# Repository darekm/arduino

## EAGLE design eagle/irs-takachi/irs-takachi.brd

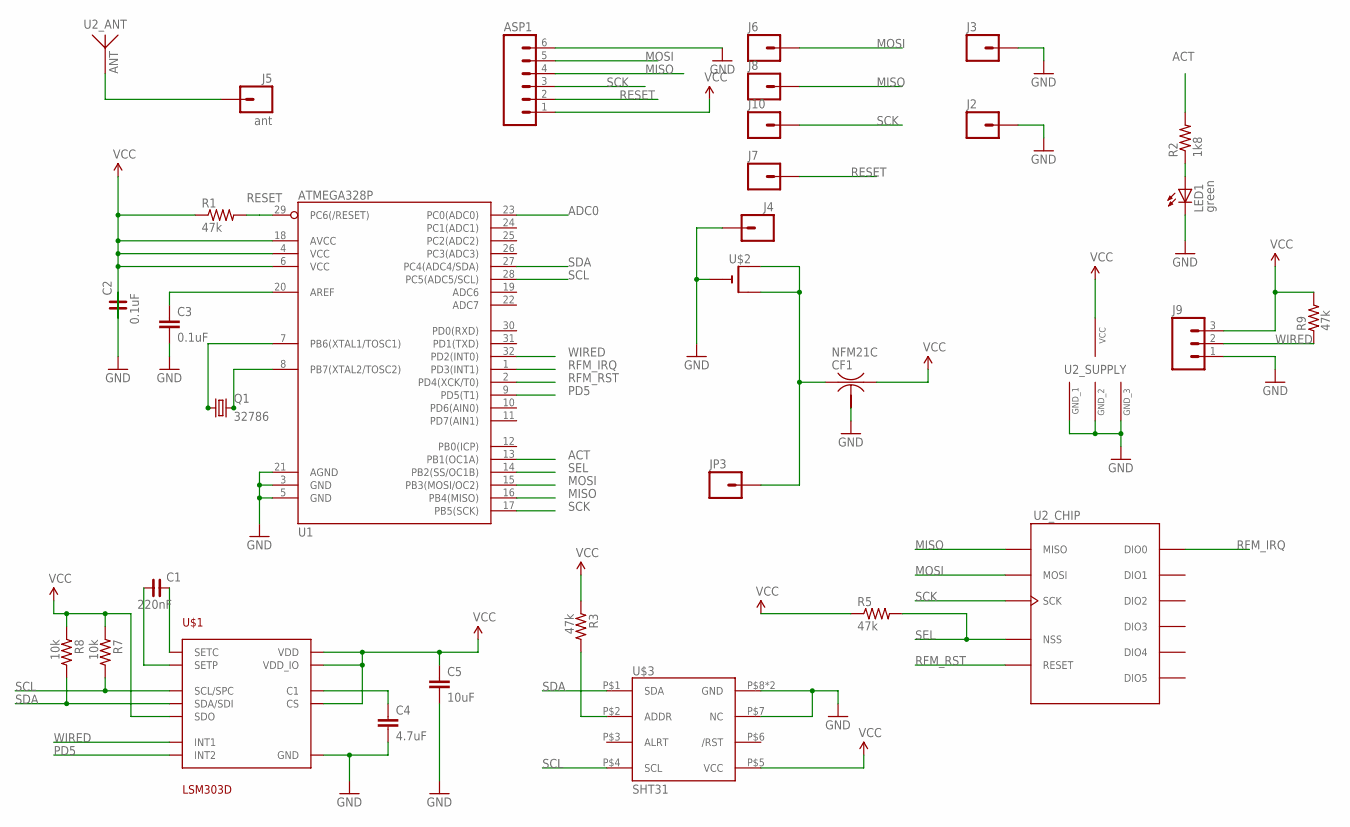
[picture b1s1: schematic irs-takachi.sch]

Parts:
ASP1: M06NO_SILK_YES_STOP; 1X06_NO_SILK_YES_STOP
C1: 220nF; C0603
C2: 0.1uF; C0603
C3: 0.1uF; 0603-CAP
C4: 4.7uF; C0603K
C5: 10uF; 0805-CAP
CF1: NFM21C
J2, J3: M01PTH_NO_SILK_YES_STOP; 1X01_NO_SILK
J4: M01SNAP-FEMALE; SNAP-FEMALE
J5: ant; 1X01_NO_SILK
J6, J7, J8, J10: M01SMD-4.5X1.5; PAD-1.5X4.5
J9: M031X03_NO_SILK; 1X03_NO_SILK
JP3: M01SMDNS; 1X01NS
LED1: green; LED-0603
Q1: 32786; MC-306
R1, R5: 47k; 0603-RES
R2: 1k8; 0603-RES
R3, R9: 47k; R0603
R7, R8: 10k; R0603
U1: ATMEGA328P; TQFP32-08
U2: RFM69HCW-S2; HOPE-RF-16
U$1: LSM303D; LGA16-3MM
U$2: CR2032THM; CR2032-THRU
U$3: SHT31; SHT3X

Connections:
ACT: R2.2, U1.13 (PB1(OC1A))
ADC0: U1.23 (PC0(ADC0))
GND: ASP1.6, C2.2, C3.2, C4.2, C5.2, CF1.2@1 (2), J2.1, J3.1, J4.1, J9.1, LED1.C, U1.3 (GND), U1.5 (GND), U1.21 (AGND), U2.GND1 (GND_1), U2.GND2 (GND_2), U2.GND3 (GND_3), U$1.5 (GND), U$1.10 (GND), U$1.12 (GND), U$1.13 (GND), U$1.16 (GND), U$2.-, U$3.P$7 (NC), U$3.P$8 (GND), U$3.PAD (GND)
MISO: ASP1.4, J8.P$1, U1.16 (PB4(MISO)), U2.MISO
MOSI: ASP1.5, J6.P$1, U1.15 (PB3(MOSI/OC2)), U2.MOSI
unnamed: LED1.A, R2.1
unnamed: CF1.1, JP3.1, U$2.+1 (+), U$2.+2 (+1)
unnamed: J5.1, U2.ANT
unnamed: C3.1, U1.20 (AREF)
unnamed: Q1.1, U1.7 (PB6(XTAL1/TOSC1))
unnamed: Q1.4 (2), U1.8 (PB7(XTAL2/TOSC2))
unnamed: C1.1, U$1.3 (SETP)
unnamed: C1.2, U$1.2 (SETC)
unnamed: C4.1, U$1.15 (C1)
unnamed: R3.2, U$3.P$2 (ADDR)
PD5: U1.9 (PD5(T1)), U$1.9 (INT2)
RESET: ASP1.2, J7.P$1, R1.2, U1.29 (PC6(/RESET))
RFM_IRQ: U1.1 (PD3(INT1)), U2.DIO0
RFM_RST: U1.2 (PD4(XCK/T0)), U2.RESET
SCK: ASP1.3, J10.P$1, U1.17 (PB5(SCK)), U2.SCK
SCL: R7.2, U1.28 (PC5(ADC5/SCL)), U$1.4 (SCL/SPC), U$3.P$4 (SCL)
SDA: R8.2, U1.27 (PC4(ADC4/SDA)), U$1.6 (SDA/SDI), U$3.P$1 (SDA)
SEL: R5.2, U1.14 (PB2(SS/OC1B)), U2.NSS
VCC: ASP1.1, C2.1, C5.1, CF1.3, J9.3, R1.1, R3.1, R5.1, R7.1, R8.1, R9.2, U1.4 (VCC), U1.6 (VCC), U1.18 (AVCC), U2.3.3V (VCC), U$1.1 (VDD_IO), U$1.7 (SDO), U$1.8 (CS), U$1.14 (VDD), U$3.P$5 (VCC)
WIRED: J9.2, R9.1, U1.32 (PD2(INT0)), U$1.11 (INT1)

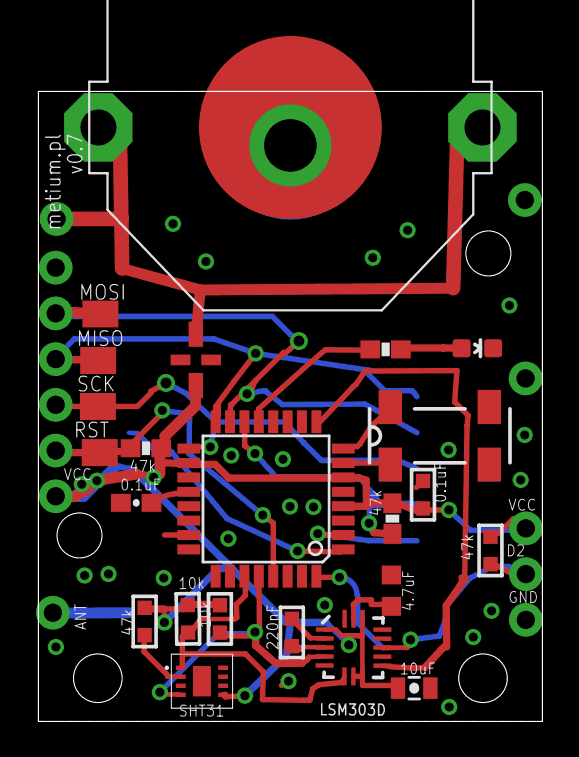
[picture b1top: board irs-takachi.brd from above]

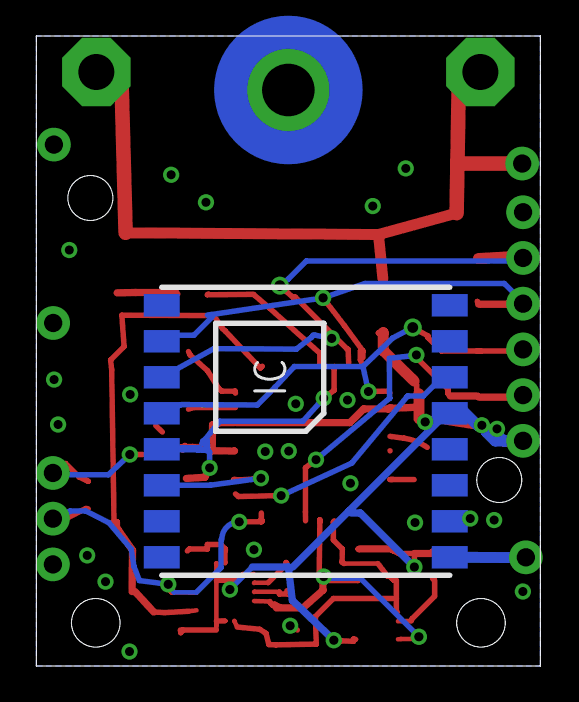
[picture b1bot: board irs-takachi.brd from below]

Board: 2 copper layers, 28.0 x 35.0 mm, 31 parts (3 on the bottom side), 24 nets.

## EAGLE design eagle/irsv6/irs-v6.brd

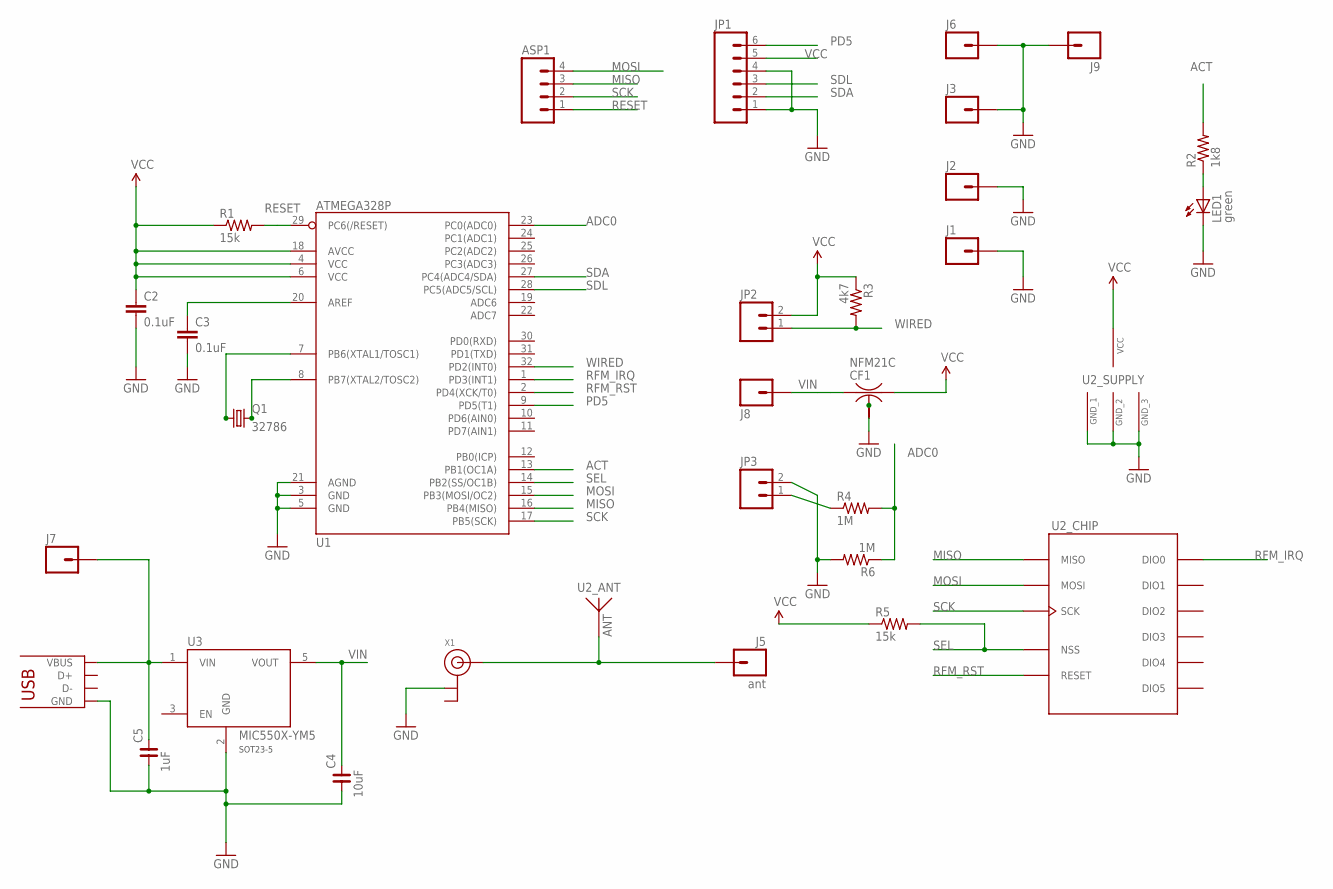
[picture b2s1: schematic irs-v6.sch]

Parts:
ASP1: M04NO_SILK_ALL_ROUND; 1X04_NO_SILK_ALL_ROUND
C2, C3: 0.1uF; 0603-CAP
C4: 10uF; C0805
C5: 1uF; C0805
CF1: NFM21C
J1, J2, J3, J6, J7, J8, J9: M01PTH_NO_SILK_YES_STOP; 1X01_NO_SILK
J4: USB-REVERSE-MICROB; USB-MICROB
J5: ant; 1X01_NO_SILK
JP1: M06NO_SILK_FEMALE_PTH; 1X06_NO_SILK
JP2, JP3: M021X02_NO_SILK; 1X02_NO_SILK
LED1: green; LED-0603
Q1: 32786; MC-306
R1, R5: 15k; 0603-RES
R2: 1k8; 0603-RES
R3: 4k7; 0603-RES
R4, R6: 1M; 0603-RES
U1: ATMEGA328P; TQFP32-08
U2: RFM69HCW-S2; HOPE-RF-16
U3: MIC550X-YM5; SOT23-5-DBV
X1: ANTENNA_U.FL; U.FL

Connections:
ACT: R2.2, U1.13 (PB1(OC1A))
ADC0: R4.2, R6.1, U1.23 (PC0(ADC0))
GND: C2.2, C3.2, C4.1, C5.1, CF1.2@1 (2), J1.1, J2.1, J3.1, J4.MT1 (GND), J4.MT2 (GND), J4.VBUS (GND), J6.1, J9.1, JP1.1, JP1.4, JP3.2, LED1.C, R6.2, U1.3 (GND), U1.5 (GND), U1.21 (AGND), U2.GND1 (GND_1), U2.GND2 (GND_2), U2.GND3 (GND_3), U3.2 (GND), X1.1 (GND)
MISO: ASP1.3, U1.16 (PB4(MISO)), U2.MISO
MOSI: ASP1.4, U1.15 (PB3(MOSI/OC2)), U2.MOSI
unnamed: LED1.A, R2.1
unnamed: JP3.1, R4.1
unnamed: J5.1, U2.ANT, X1.3 (SIGNAL)
unnamed: C3.1, U1.20 (AREF)
unnamed: Q1.1, U1.7 (PB6(XTAL1/TOSC1))
unnamed: Q1.4 (2), U1.8 (PB7(XTAL2/TOSC2))
unnamed: C5.2, J4.GND (VBUS), J7.1, U3.1 (VIN)
PD5: JP1.6, U1.9 (PD5(T1))
RESET: ASP1.1, R1.2, U1.29 (PC6(/RESET))
RFM_IRQ: U1.1 (PD3(INT1)), U2.DIO0
RFM_RST: U1.2 (PD4(XCK/T0)), U2.RESET
SCK: ASP1.2, U1.17 (PB5(SCK)), U2.SCK
SDA: JP1.2, U1.27 (PC4(ADC4/SDA))
SDL: JP1.3, U1.28 (PC5(ADC5/SCL))
SEL: R5.2, U1.14 (PB2(SS/OC1B)), U2.NSS
VCC: C2.1, CF1.3, JP1.5, JP2.2, R1.1, R3.1, R5.1, U1.4 (VCC), U1.6 (VCC), U1.18 (AVCC), U2.3.3V (VCC)
VIN: C4.2, CF1.1, J8.1, U3.5 (VOUT)
WIRED: JP2.1, R3.2, U1.32 (PD2(INT0))

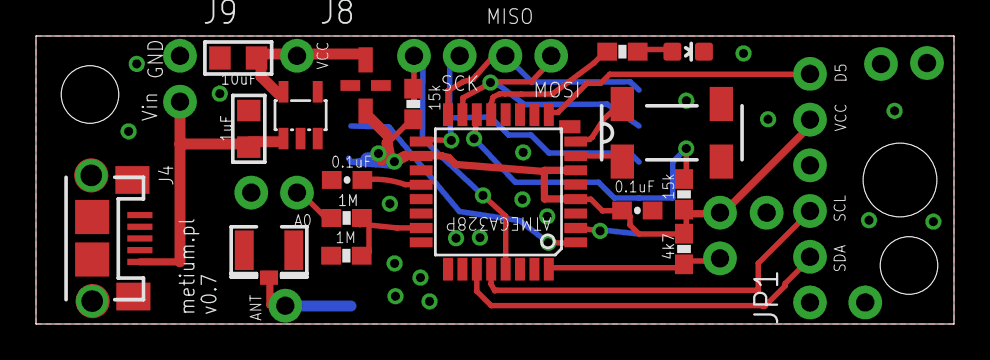
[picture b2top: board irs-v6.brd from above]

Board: 2 copper layers, 51.0 x 16.0 mm, 30 parts (1 on the bottom side), 23 nets.

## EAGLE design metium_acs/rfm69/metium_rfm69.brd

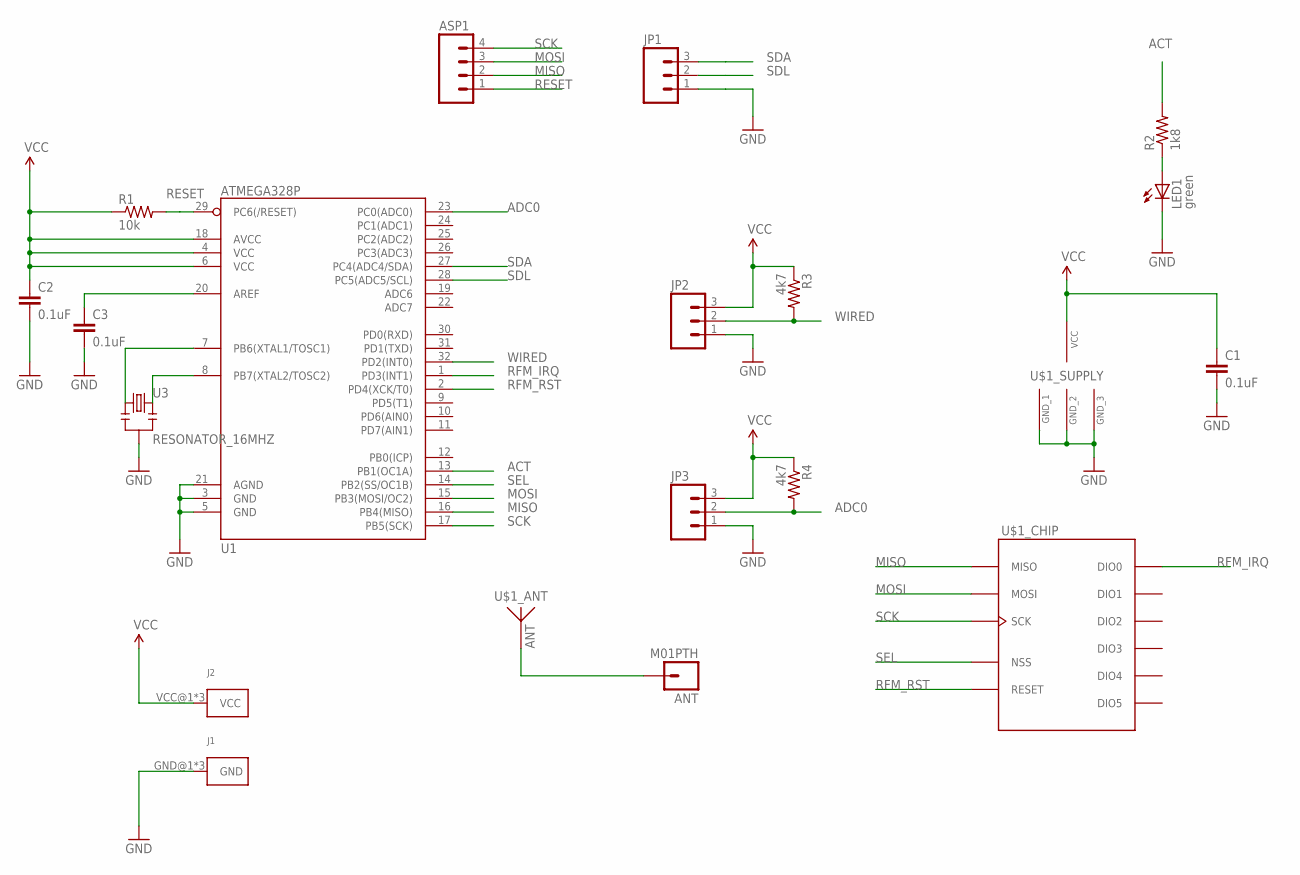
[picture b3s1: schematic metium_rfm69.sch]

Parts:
ANT: M01PTH; 1X01
ASP1: M04PTH; 1X04
C1, C2, C3: 0.1uF; 0603-CAP
J1: KEYSTONE-629; KEYSTONE_AA_AAA_BATTERY_TERMINAL-629
J2: KEYSTONE-637; KEYSTONE_AA_AAA_BATTERY_TERMINAL-637
JP1, JP2, JP3: M03PTH; 1X03
LED1: green; LED-0603
R1: 10k; 0603-RES
R2: 1k8; 0603-RES
R3, R4: 4k7; 0603-RES
U1: ATMEGA328P; TQFP32-08
U3: RESONATOR_16MHZ; RESONATOR_SMD
U$1: RFM69HCW-S2; HOPE-RF-16

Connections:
ACT: R2.2, U1.13 (PB1(OC1A))
ADC0: JP3.2, R4.2, U1.23 (PC0(ADC0))
GND: C1.2, C2.2, C3.2, J1.GND@1, J1.GND@2, J1.GND@3, JP1.1, JP2.1, JP3.1, LED1.C, U1.3 (GND), U1.5 (GND), U1.21 (AGND), U3.2, U$1.GND1 (GND_1), U$1.GND2 (GND_2), U$1.GND3 (GND_3)
MISO: ASP1.2, U1.16 (PB4(MISO)), U$1.MISO
MOSI: ASP1.3, U1.15 (PB3(MOSI/OC2)), U$1.MOSI
unnamed: LED1.A, R2.1
unnamed: ANT.1, U$1.ANT
unnamed: C3.1, U1.20 (AREF)
unnamed: U1.7 (PB6(XTAL1/TOSC1)), U3.1
unnamed: U1.8 (PB7(XTAL2/TOSC2)), U3.3
RESET: ASP1.1, R1.2, U1.29 (PC6(/RESET))
RFM_IRQ: U1.1 (PD3(INT1)), U$1.DIO0
RFM_RST: U1.2 (PD4(XCK/T0)), U$1.RESET
SCK: ASP1.4, U1.17 (PB5(SCK)), U$1.SCK
SDA: JP1.3, U1.27 (PC4(ADC4/SDA))
SDL: JP1.2, U1.28 (PC5(ADC5/SCL))
SEL: U1.14 (PB2(SS/OC1B)), U$1.NSS
VCC: C1.1, C2.1, J2.VCC@1, J2.VCC@2, J2.VCC@3, JP2.3, JP3.3, R1.1, R3.1, R4.1, U1.4 (VCC), U1.6 (VCC), U1.18 (AVCC), U$1.3.3V (VCC)
WIRED: JP2.2, R3.2, U1.32 (PD2(INT0))

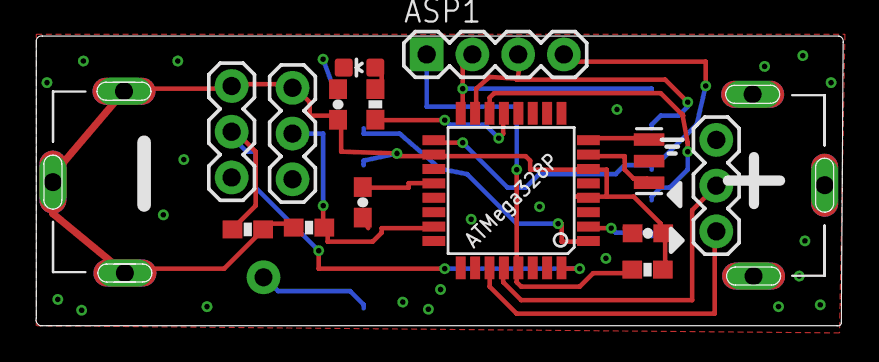
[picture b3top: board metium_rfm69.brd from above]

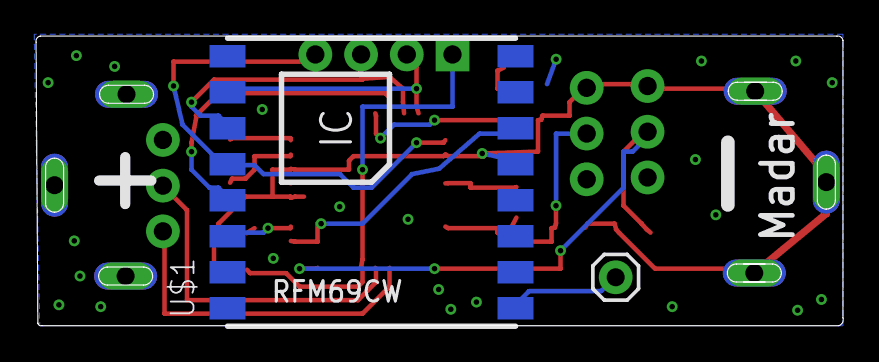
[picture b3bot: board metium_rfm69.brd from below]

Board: 2 copper layers, 44.8 x 16.1 mm, 18 parts (2 on the bottom side), 19 nets.

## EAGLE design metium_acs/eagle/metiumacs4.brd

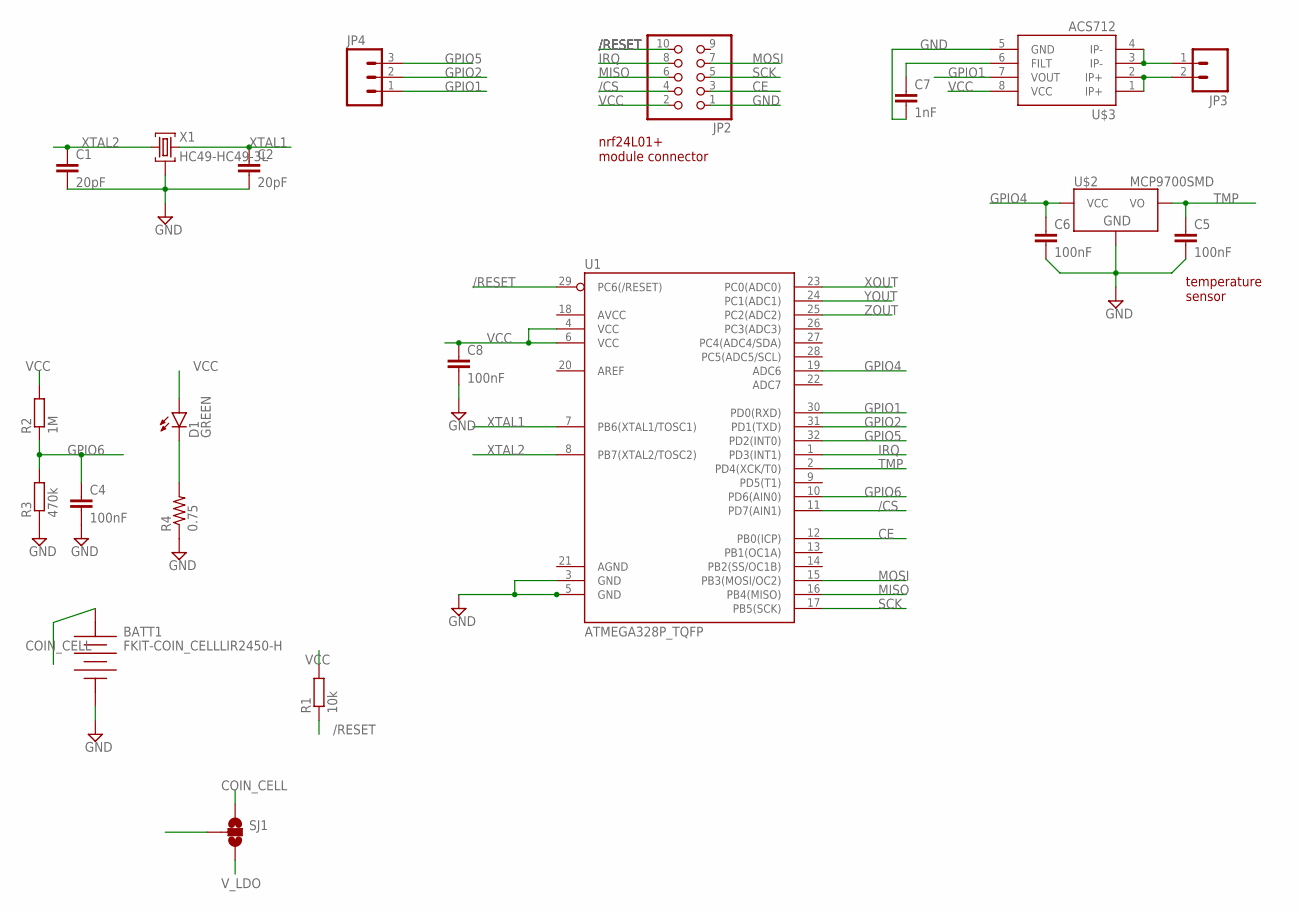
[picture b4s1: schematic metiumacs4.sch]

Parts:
BATT1: FKIT-COIN_CELLLIR2450-H; FKIT-LIR2450-H
C1, C2: 20pF; 0805
C4, C5, C6: 100nF; C0805
C7: 1nF; 0603-CAP
C8: 100nF; 0805
D1: GREEN; LED-0603
JP2: PINHD-2X5; 2X05M
JP3: M02PTH4; 1X02_XTRA_BIG
JP4: M03LONGPADS; 1X03_LONGPADS
R1: 10k; R0805
R2: 1M; R0805
R3: 470k; R0805
R4: 0.75; 0805
SJ1: SOLDERJUMPER_2WAYS; SJ_3
U1: ATMEGA328P_TQFP; TQFP32-08
U$2: MCP9700SMD; SOT23-3
U$3: ACS712; SO08
X1: HC49-HC49-3L; HC49-3L

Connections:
/CS: JP2.4, U1.11 (PD7(AIN1))
/RESET: JP2.10, R1.1, U1.29 (PC6(/RESET))
CE: JP2.3, U1.12 (PB0(ICP))
COIN_CELL: BATT1.POS, SJ1.1
FS1: JP3.1, U$3.3 (IP-), U$3.4 (IP-)
FS2: JP3.2, U$3.1 (IP+), U$3.2 (IP+)
GND: BATT1.NEG, C1.2, C2.2, C4.2, C5.2, C6.2, C7.2, C8.2, JP2.1, R3.1, R4.1, U1.3 (GND), U1.5 (GND), U$2.3 (GND), U$3.5 (GND), X1.2
GPIO1: JP4.1, U1.30 (PD0(RXD)), U$3.7 (VOUT)
GPIO2: JP4.2, U1.31 (PD1(TXD))
GPIO4: C6.1, U1.19 (ADC6), U$2.1 (VCC)
GPIO5: JP4.3, U1.32 (PD2(INT0))
GPIO6: C4.1, R2.1, R3.2, U1.10 (PD6(AIN0))
IRQ: JP2.8, U1.1 (PD3(INT1))
MISO: JP2.6, U1.16 (PB4(MISO))
MOSI: JP2.7, U1.15 (PB3(MOSI/OC2))
unnamed: C7.1, U$3.6 (FILT)
unnamed: D1.C, R4.2
SCK: JP2.5, U1.17 (PB5(SCK))
TMP: C5.1, U1.2 (PD4(XCK/T0)), U$2.2 (VO)
VCC: C8.1, D1.A, JP2.2, R1.2, R2.2, SJ1.2, U1.4 (VCC), U1.6 (VCC), U$3.8 (VCC)
V_LDO: SJ1.3
XOUT: U1.23 (PC0(ADC0))
XTAL1: C2.1, U1.7 (PB6(XTAL1/TOSC1)), X1.3
XTAL2: C1.1, U1.8 (PB7(XTAL2/TOSC2)), X1.1
YOUT: U1.24 (PC1(ADC1))
ZOUT: U1.25 (PC2(ADC2))

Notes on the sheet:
nrf24L01+ module connector
temperature sensor

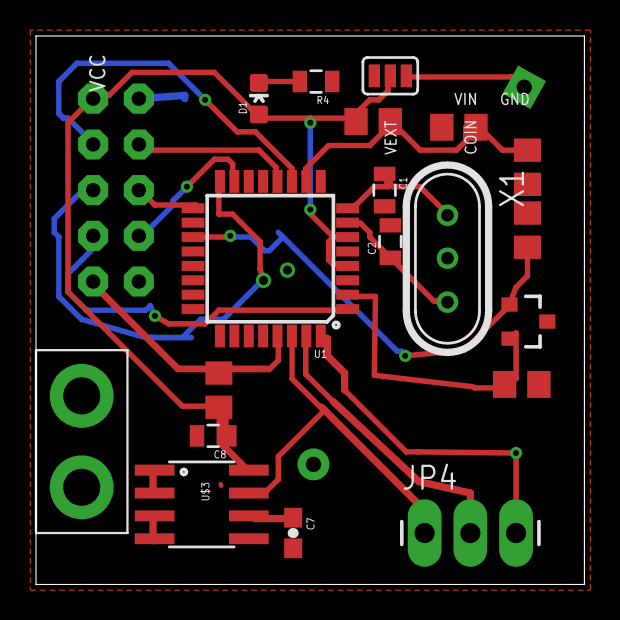
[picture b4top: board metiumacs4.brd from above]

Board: 2 copper layers, 30.5 x 30.5 mm, 21 parts (1 on the bottom side), 22 nets.

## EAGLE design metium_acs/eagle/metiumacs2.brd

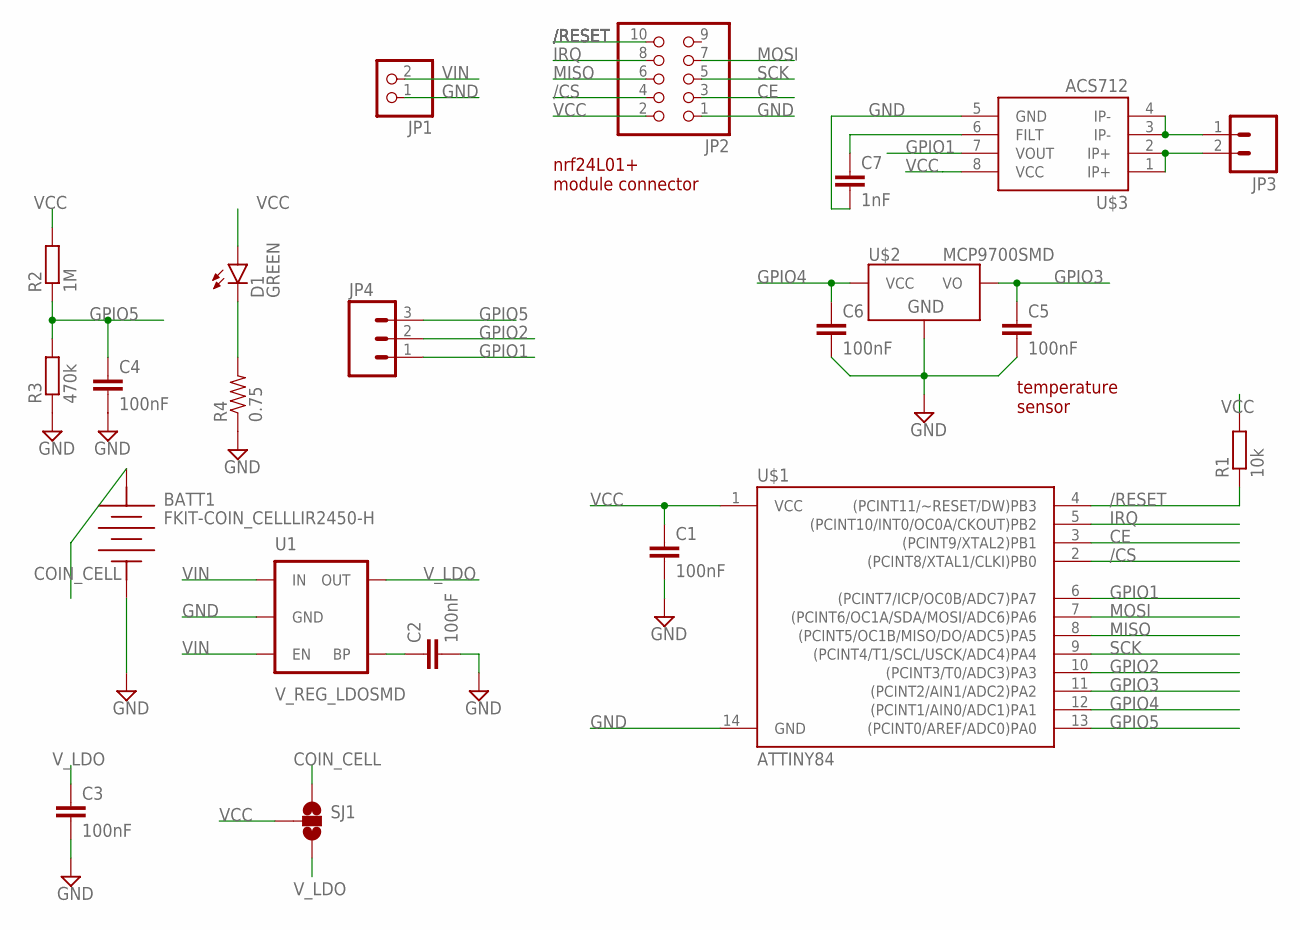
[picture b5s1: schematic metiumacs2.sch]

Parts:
BATT1: FKIT-COIN_CELLLIR2450-H; FKIT-LIR2450-H
C1, C2, C3, C4, C5, C6: 100nF; C0805
C7: 1nF; 0603-CAP
D1: GREEN; LED-0603
JP1: HEADER-1X2ROUND; 1X02_ROUND
JP2: PINHD-2X5; 2X05M
JP3: M02PTH4; 1X02_XTRA_BIG
JP4: M03LONGPADS; 1X03_LONGPADS
R1: 10k; R0805
R2: 1M; R0805
R3: 470k; R0805
R4: 0.75; 0805
SJ1: SOLDERJUMPER_2WAYS; SJ_3
U1: V_REG_LDOSMD; SOT23-5
U$1: ATTINY84; SO14
U$2: MCP9700SMD; SOT23-3
U$3: ACS712; SO08

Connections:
/CS: JP2.4, U$1.2 ((PCINT8/XTAL1/CLKI)PB0)
/RESET: JP2.10, R1.1, U$1.4 ((PCINT11/~RESET/DW)PB3)
CE: JP2.3, U$1.3 ((PCINT9/XTAL2)PB1)
COIN_CELL: BATT1.POS, SJ1.1
FS1: JP3.1, U$3.3 (IP-), U$3.4 (IP-)
FS2: JP3.2, U$3.1 (IP+), U$3.2 (IP+)
GND: BATT1.NEG, C1.2, C2.2, C3.2, C4.2, C5.2, C6.2, C7.2, JP1.1, JP2.1, R3.1, R4.1, U1.2 (GND), U$1.14 (GND), U$2.3 (GND), U$3.5 (GND)
GPIO1: JP4.1, U$1.6 ((PCINT7/ICP/OC0B/ADC7)PA7), U$3.7 (VOUT)
GPIO2: JP4.2, U$1.10 ((PCINT3/T0/ADC3)PA3)
GPIO3: C5.1, U$1.11 ((PCINT2/AIN1/ADC2)PA2), U$2.2 (VO)
GPIO4: C6.1, U$1.12 ((PCINT1/AIN0/ADC1)PA1), U$2.1 (VCC)
GPIO5: C4.1, JP4.3, R2.1, R3.2, U$1.13 ((PCINT0/AREF/ADC0)PA0)
IRQ: JP2.8, U$1.5 ((PCINT10/INT0/OC0A/CKOUT)PB2)
MISO: JP2.6, U$1.8 ((PCINT5/OC1B/MISO/DO/ADC5)PA5)
MOSI: JP2.7, U$1.7 ((PCINT6/OC1A/SDA/MOSI/ADC6)PA6)
unnamed: C2.1, U1.4 (BP)
unnamed: C7.1, U$3.6 (FILT)
unnamed: D1.C, R4.2
SCK: JP2.5, U$1.9 ((PCINT4/T1/SCL/USCK/ADC4)PA4)
VCC: C1.1, D1.A, JP2.2, R1.2, R2.2, SJ1.2, U$1.1 (VCC), U$3.8 (VCC)
VIN: JP1.2, U1.1 (IN), U1.3 (EN)
V_LDO: C3.1, SJ1.3, U1.5 (OUT)

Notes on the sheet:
nrf24L01+ module connector
temperature sensor

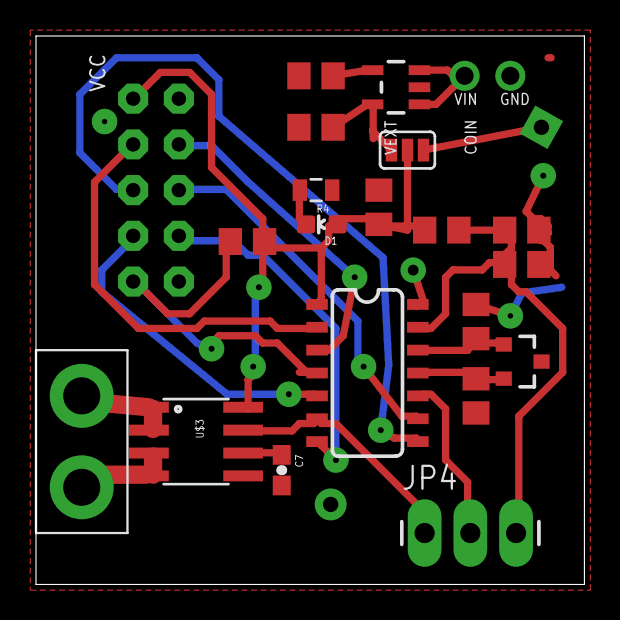
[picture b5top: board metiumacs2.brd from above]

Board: 2 copper layers, 30.5 x 30.5 mm, 22 parts (1 on the bottom side), 22 nets.

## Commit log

2015-03-09 :tada: Added .gitattributes & .gitignore files
2015-03-09 commit libraries
2015-03-13 Moisture input
2015-03-17 metium sensor foundation
2015-03-17 change .gitignore
2015-04-01 gitignore refine
2015-04-01 test
2015-04-12 schemat irs
2015-04-28 prepare for AtTiny
2015-04-28 LowPower playing
2015-05-02 prepare ver2
2015-05-03 class Frame
2015-05-29 eagle ver 4
2015-09-06 testtty foundation
2015-09-17 testCC1101
2015-09-18 remake example to use transceiver
2015-09-18 Transceiver has own buffers
2015-09-19 all function in Transceiver
2015-09-19 tableACK for acked data
2015-09-19 proper coompute crc
2015-09-21 use TableACK
2015-09-21 extract uart
2015-09-22 prepare to use imcc1101
2015-09-22 clean ino code
2015-09-23 Uart now push Frame
2015-10-03 prepare to use imwave library
2015-10-03 use interrupt to check receving
2015-10-05 project monitor
2015-10-08 monitor communicate with WIN
2015-11-09 Ino for intrappFlex device
2015-11-23 setup device Id in itransppflex
2015-11-24 Radino: send Vcc
2015-11-26 sketch for dallas ds18b20
2015-11-28 prepare cycling on datasend
2015-12-12 update ino to modifier transceiver library
2015-12-13 Example with PIR HS SR 501
2015-12-13 add TimerHelloCycle:frequency to response on Knock
2015-12-13 change time of datalogging
2015-12-28 Internal VCC on 32U4
2015-12-28 Flex sent internal vcc and charger status
2015-12-29 project soil
2016-01-01 print Transceiver status
2016-01-01 Soil: repair main loop
2016-01-04 repair bug in main LOOP
2016-01-13 async measure
2016-01-17 DS18B20: automatic MAC addres
2016-01-20 Prepare intraflex to new setupTimers
2016-01-21 remake Soil sketch
2016-02-01 Reboot function
2016-02-01 Pir: prepare to current version of timer
2016-02-02 prepare intraflex to new version of transmiter
2016-02-05 adapt to to new version of transceiver library
2016-02-06 Intrapflex : sent batery vcc
2016-02-06 Add WDT to sketch
2016-02-11 update sketch
2016-02-20 adding project crossroad
2016-02-20 Move handle interrupt totransceiver
2016-02-23 Gateway to RFM69 - first attempt
2016-02-23 Gateway - add register file
2016-03-01 Test receiver: send Flood
2016-05-07 move ISR to main file
2016-05-16 feat(rfm69) testing sketch
2016-06-09 eagle(rfm69) pcb size of 18650
2016-06-16 feat(ino) using Timer2
2016-09-13 feat(ds18b20) prepare to work with CC1101 again
2016-09-15 fix(flex) adapt to current verion of imwave
2016-09-17 feat(intrapsoil) foundation
2016-09-29 upd(core) add libraries to .gitignore
2016-09-30 testrmf69 update
2016-10-04 fix(rfm69) remove classtest : double instace of transceiver
2016-10-04 UPD intrapsoil defined
2016-10-05 feat Imwave - gateway working registers
2016-10-05 imwave-gateway fox power
2016-10-09 add(ino) timer2 sleep test
2016-10-12 add(metionacs) schemat
2016-10-15 add(atmega) script to burn bootloader
2016-10-16 upd(ino) debug pin
2016-10-17 fix(burn) refine burning scripts
2016-10-23 add(irs) new project of pcb
2016-10-27 upd(testrfm69) setup Mac number
2016-10-27 upd(eagle) recommit after merge
2016-10-27 upd(ino) to new tranceiver
2016-10-29 upd(avrdude) upload hex files
2016-10-29 fix(avrdude) update config files
2016-10-29 upd(ds18b20) store cc1101 version
2016-10-29 fix(ds18b20) update to rfm69
2016-10-29 upd(library) added OneWire
2016-10-29 upd(ds18b20) prepare to use rfm69
2016-10-29 fix(ds18b20) compute data disabled by mistake
2016-10-30 upd(ino)optimization of wakeup
2016-11-01 upd(ds18b20)remove dbg delay
2016-11-02 upd(burn) hex for ds18b20
2016-11-04 feat(ds18b20) disable ADC
2016-11-23 fix(ds18b20) prepare to sleep ADC
2016-11-26 add(clock32) sketch for clystal32k
2016-11-27 feat(clock32)sleep on 53.3 uA, 128Hz
    OCR1A=15; 128Hz
2016-11-28 fix(clock32k) clean up
2016-11-28 fix(tranceiver) 150uA when connected
2016-12-02 upd(burn) ds18b20 v.Clock32k
2016-12-05 upd(git) attribute autocrlf
2016-12-05 add(acs720) foundation
2016-12-22 power_timer0_enable
2016-12-24 upd(testrfm) delay on startup
2016-12-24 upd(ds18b20) disable powersave on startup
2016-12-26 add(mhx711) foundation tensometr sensor
2016-12-28 Create ismv1
2016-12-28 wired: version V1
2017-01-12 MAX6675 :thermocouple foundation
2017-01-12 hx711 : adapt to ICS board
2017-01-16 MAX6675 run with ICS
2017-01-21 use eeprom
2017-01-27 max6675: delay on start measure
2017-01-29 prepare HX711 to protocol v.9 with eeprom
2017-02-01 ds18b20: resetPn on startup
2017-02-09 sketch :: HMC5883L sensor
2017-02-09 MHC583l: trigger
2017-02-18 acs720: sinus measure
2017-02-18 ACS720 - testing sketch
2017-02-21 upd(acs720) variable supply
2017-02-21 acs720 complete sketch
2017-02-23 testGY271 foundation
2017-02-25 acs20- measure 40ms =41 cycles
2017-02-25 acs: disable ACD on sleep
2017-02-25 irs: eagle project
2017-02-26 hmc5883l : compute step average
2017-03-03 testRFT69: add blinking LED
2017-03-20 MHMC: lowing power
2017-03-21 acs: low amps to 30uA
2017-03-24 ds18b20: internal temp
2017-03-24 burn: update hex
2017-03-24 upload boot atmega
2017-03-26 mmax6675: low power
2017-04-05 ino: remove ERRLED scripts
2017-04-07 heartrate: foundation
2017-04-08 hertrate: now working
2017-04-10 acs712: measure vcc
2017-04-23 heartrate: send all data
2017-04-23 ds18b20: remove pinLed
2017-04-26 hertrate: sendDataAll
2017-05-11 heartRate: stepDown algorithm
2017-05-13 update(heart) algorithm min average
2017-05-14 heartrate:detection algorithm
2017-06-01 eagle: add version 5 of board
2017-06-27 adxl345 foundation
2017-06-27 adxl345: adapt adafruit library
2017-06-30 adxl346:interup
2017-07-02 hx711: testing
2017-07-02 adxl345: FIFO interrupt
2017-07-19 adxl345: specify connections
2017-07-22 mmax345: compute minmax value
2017-07-23 soilly38: foundation
2017-07-25 max6675:clean source
2017-07-25 soil: adc turn on
2017-08-21 lsm303Lib foundation
2017-08-26 lsm303: use pololu library
2017-08-26 lsm303: check chip
2017-09-07 lsm303: inertial int
2017-09-08 lsm303:interrupt on magnetometer
2017-09-09 lsm303 :interrupt on FIFO
2017-09-09 lsm303:set FIFO threshold
2017-09-11 sht31: foundation
2017-09-14 SHT31- sleeping
2017-09-14 adxl345:deeper sleeping
2017-09-20 acs720: update channel
2017-09-23 timer2sleep: upgrade
2017-09-26 INO: stopListenBroadcast in main loop
2017-10-21 lsm303d:server address
2017-11-02 sht31: prepare to PCB 0.8
2017-11-02 ds18b20: update serverMAC
2017-11-15 sht: VCC measure
2017-11-17 mhmc: measure vcc
2017-11-17 adxl345: fix knock
2017-11-21 lsm303: send data
2017-11-27 acs720: update
2017-12-12 qtoouchadc:initial
2017-12-12 lsm303:read magnetic sensor
2017-12-12 soilyl38:internal temperature
2017-12-13 qtouch:light 3 leds
2017-12-13 qtouch: 3 sensors switch light
2017-12-15 qswitch:foundation
2017-12-15 qSwitch: set 100ms interval data flood
2017-12-28 qswitch:get order
2017-12-28 qtouch: foundation
2018-01-02 qtest: send frame on change
2018-01-02 qtouch:measure shift
2018-01-05 qtouch: compute shift limit
2018-01-08 soil38:measure VCC
2018-01-12 ds18b20:adapt to switch
2018-01-18 qtouch:average shift
2018-02-03 lsm303fht:foundation
2018-02-22 lsmFHT: lin8 output
2018-02-26 mhx711:format code
2018-02-26 soil: prepare to platformio
2018-03-02 lsm303fht:disableADCB
2018-03-20 lsm303:update driver
2018-03-24 lsm303:cyclic measure
2018-03-29 lsm303: sensor power down
2018-03-29 lsm303:disable pullap
2018-03-29 soiladc:foundation
2018-03-31 soiladc:senseadctwice
2018-04-03 soiladc:minmax
2018-04-05 soily38: reset ADC
2018-04-06 soiladc: cyclic measure
2018-04-10 soiladc: use interrupt
2018-04-10 sht31:shutoff ADC
2018-04-14 lsm303:initialize
2018-04-17 lsm303fht:checkDisableLSM
2018-04-24 lsm303d:filtering
2018-05-08 fusesl00 foundation
2018-05-10 mhmc:update to current imwave
2018-05-10 lsm303fht: compute average
2018-05-10 hearrate: archiwize
2018-05-12 soil: first commit from VCS
2018-05-15 qtouch: archiwize address changes
2018-05-15 soiladc: change electrode pin
2018-05-15 INO: update addresses
2018-05-17 lsm303:compute mean
2018-05-17 fusessl00: low power
2018-05-22 soilADC: const shift
2018-05-24 fusesl00: 3 channels
2018-06-04 fusegate: initial
2018-06-04 fusegate: parse shadow
2018-06-05 fuse: setup protocol
2018-06-05 fusegate:parse frames on shadow
2018-06-06 fasegate:transmit fuse count
2018-06-11 fusesl00:measure phrase
2018-06-17 fusesl00: light on blown fuse in 3ph
2018-06-17 fusegate: lighn on when blown fuse
2018-06-17 fusegate:send fuses count
2018-06-20 soiladc: dummy read ADC after wakeup
2018-07-12 fusegate:decTable
2018-07-12 fusegate:not false messages
2018-07-12 fusegate: swtch to sendMessage
2018-07-12 fusegate:enable 3 red LED
2018-07-29 fusegate: adapt to Meanwell supply
2018-07-29 fusesl00: change fuses pinout
2018-07-30 fgusesl00: green/red led
2018-08-29 add irs-lsm303d eagle Signed-off-by: Pawel B <pawelb@madar.com.pl>
2018-08-29 add irs-qtouch Signed-off-by: Pawel B <madar.com.pl>
2018-08-29 add irs-v8 Signed-off-by: Pawel B <madar.com.pl>
2018-08-29 add takachi Signed-off-by: Pawel B <madar.com.pl>
2018-08-29 add irs-v6 Signed-off-by: Pawel B <alamadar.com.pl>
2018-10-02 simplerfm foundation
2019-11-15 acs: set ADMUX after SetupADC
2019-11-22 sht10:refine setup
2019-11-30 sht31: led off before reboot
2019-12-12 create yhdc720
2019-12-23 yhdc730: add MeasureTab
2020-01-02 yhdc720: waitassr during adc measure
2020-01-27 yhdc:remove clear sum
2020-01-31 elktemp485 foundation
2020-02-01 elktemp : send to Serial
2020-02-06 elektemp: receive response
2020-02-20 modbud485: initial implementation
2020-02-21 modbus: use library
2020-04-13 install: makelink.bat creation
2020-04-13 featr:unique id
2020-04-23 ydhc720: extract measureACS720
2020-04-23 ydhc720: clean unused code
2020-04-23 yhdc: use ComputeACS on cycle
2020-05-21 remove old projects
2020-05-21 elktemp: finnish commit
2020-05-21 testrfm: update repo
2021-04-15 modbus: deploy
2021-04-15 modpus: cyclic poolCHeck
2021-04-15 fuses: waitassr
2021-04-15 lsm: enableLSM
2021-04-15 ydhc720:disable ADC average
2021-04-15 solidadc: add library

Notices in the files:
parts and their libraries:
SparkFun-DigitalIC: Licensing: Creative Commons ShareAlike 4.0 International - https://creativecommons.org/licenses/by-sa/4.0
icmi-custom-parts: ICMI Custom Parts for EAGLE by Hendrik Busch is licensed under a Creative Commons
Attribution-NonCommercial-ShareAlike 3.0 Germany License.
